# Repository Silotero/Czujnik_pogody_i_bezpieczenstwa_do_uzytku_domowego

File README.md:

# Czujnik_pogody_i_bezpieczenstwa_do_uzytku_domowego
This is a device packed with MQ-7 (CO gas sensor), MQ-2 (smoke sensor), IR fire detector, as well as AHT20 (temperature and humidity sensor), along with the BMP280 (pressure sensor).

It is battery powered with USB-C non PD charging, usiong the MCP73831 battery charge IC, capable of charging the battery with 500 mA, with an AP9101 battery protection IC. The microcontroller used in this project is a barebone ESP32-C3, with external 4 MB of FLASH memory, using QSPI. The power coming from the battery gets passed to the PAM2423 boost converter circuit that boosts the battery voltage up to 5V. The 2 devices that use 5V (MQ-7 and MQ-2) are powered directly out of that output, while the rest such as the ESP32-C3, its FLASH memory, along with the AHT20 and BMP280 gets their 3.3V voltage out of a AP2114HA LDO

The ESP32-C3 RF pin is connected to an external antenna connector (IPEX4), used for transmitting data wirelessly.

The project is meant for use with a MQTT setup for data collection on a server type device.

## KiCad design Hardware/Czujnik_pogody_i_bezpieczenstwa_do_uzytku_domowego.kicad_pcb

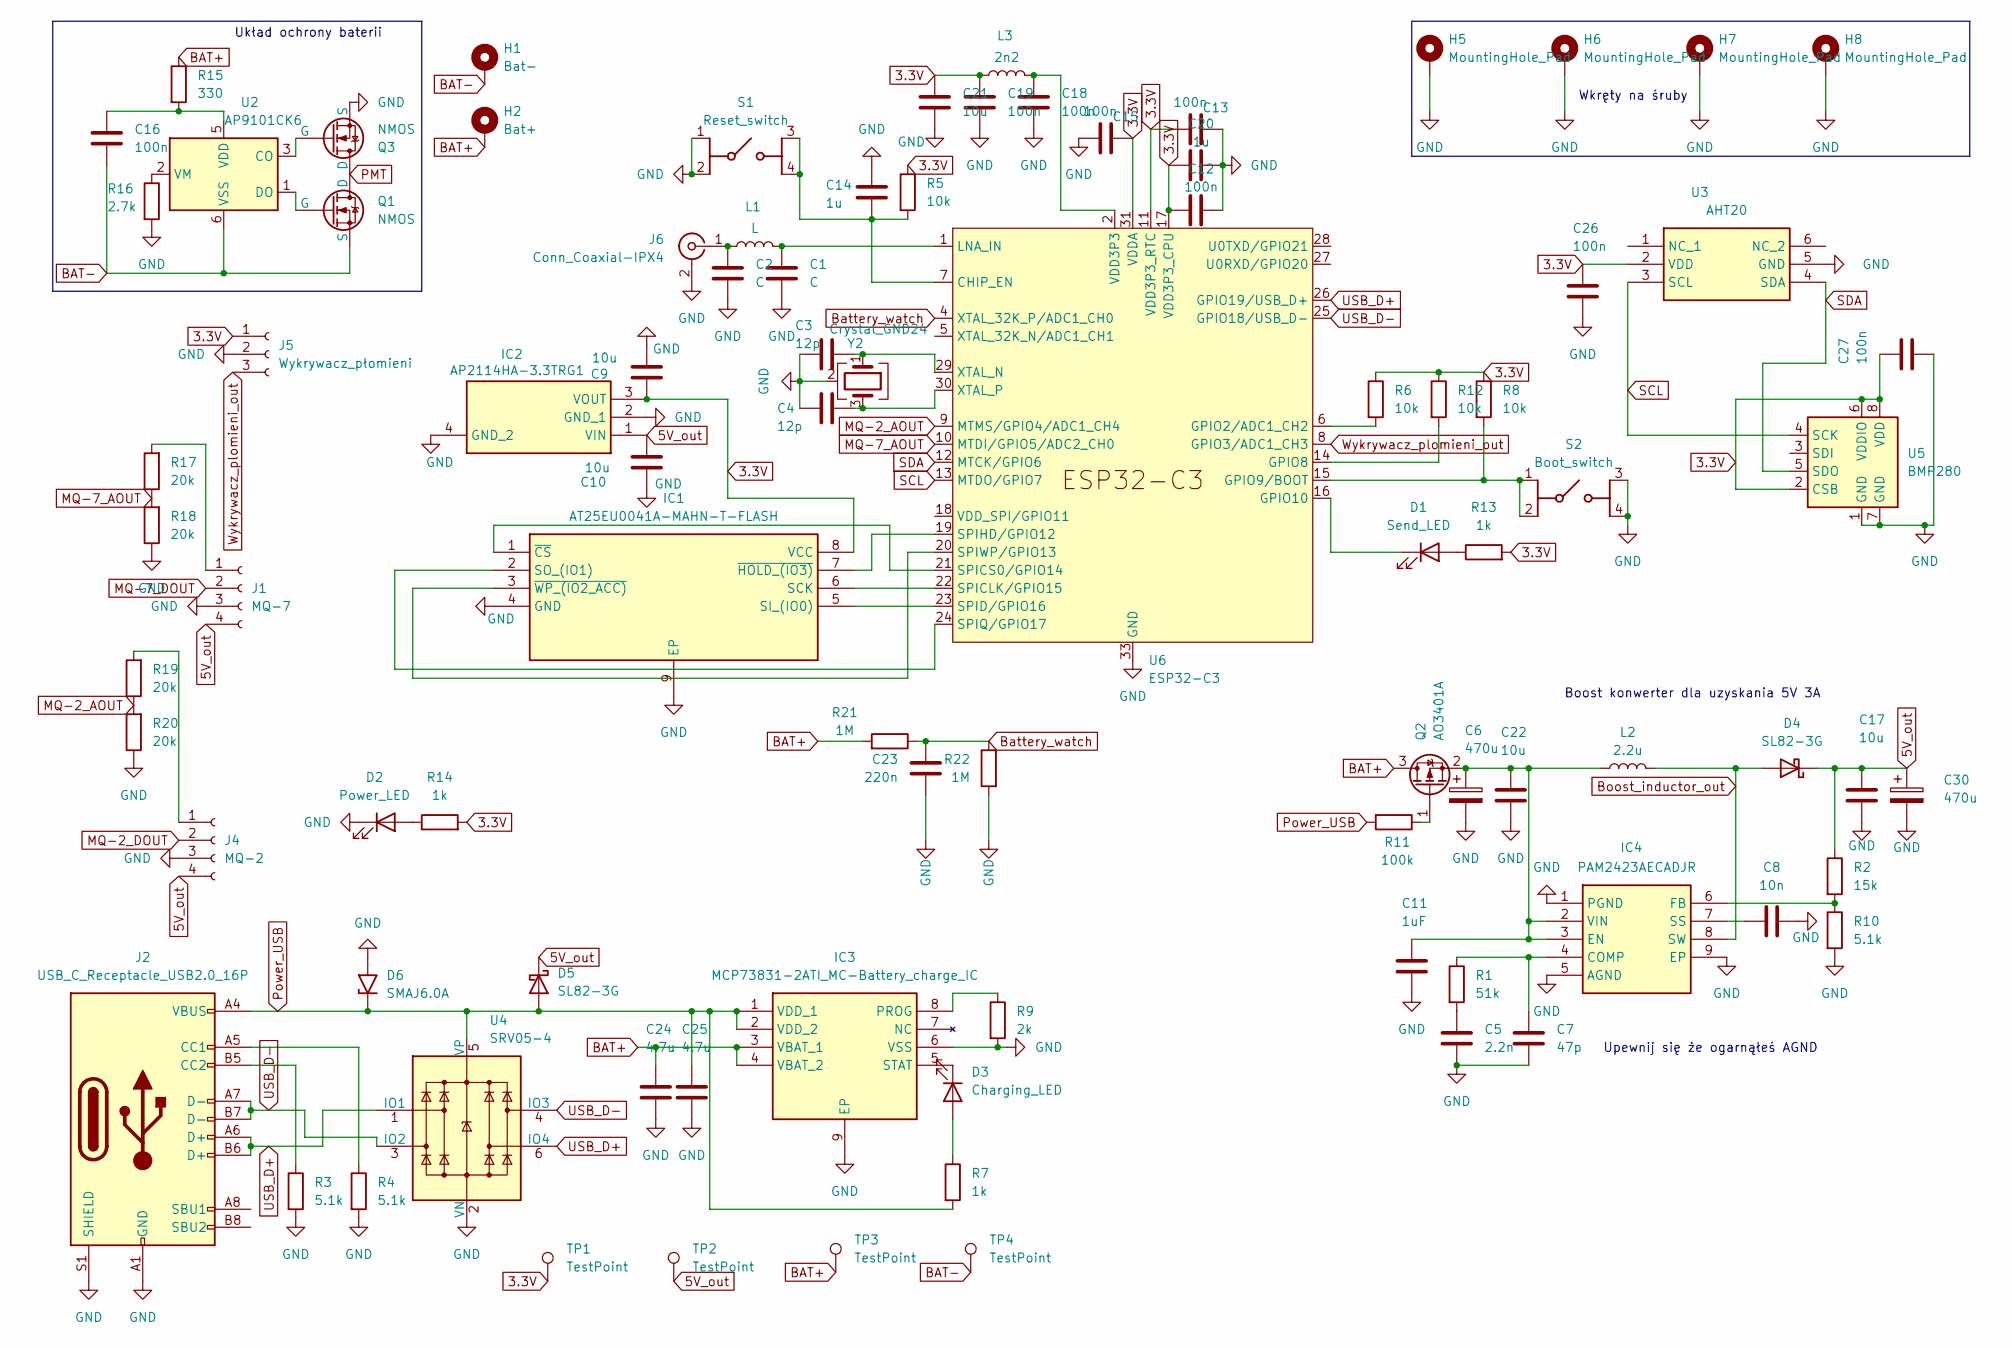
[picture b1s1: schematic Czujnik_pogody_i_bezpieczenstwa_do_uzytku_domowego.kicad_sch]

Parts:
C1, C2: C; C_0603_1608Metric
C3, C4: 12p; C_0603_1608Metric
C5: 2.2n; C_0603_1608Metric
C6, C30: 470u; CP_Radial_D10.0mm_P5.00mm
C7: 47p; C_0603_1608Metric
C8: 10n; C_0603_1608Metric
C9, C10, C17, C21, C22: 10u; C_0603_1608Metric
C11: 1uF; C_0603_1608Metric
C12, C13, C15, C16, C18, C19, C26, C27: 100n; C_0603_1608Metric
C14, C20: 1u; C_0603_1608Metric
C23: 220n; C_0603_1608Metric
C24, C25: 4.7u; C_0603_1608Metric
D1: Send_LED; LED_0603_1608Metric
D2: Power_LED; LED_0603_1608Metric
D3: Charging_LED; LED_0603_1608Metric
D4, D5: SL82-3G; D_SMC
D6: SMAJ6.0A; D_SMA
H1: Bat-; MountingHole_2.2mm_M2_DIN965_Pad_TopBottom
H2: Bat+; MountingHole_2.2mm_M2_DIN965_Pad_TopBottom
H5, H6, H7, H8: MountingHole_Pad; MountingHole_2.2mm_M2_DIN965_Pad
IC1: AT25EU0041A-MAHN-T-FLASH; SON50P300X200X60-9N-D; Manufacturer_Part_Number AT25EU0041A-MAHN-T; Mouser Part Number 968-AT25EU0041AMAHNT
IC2: AP2114HA-3.3TRG1; SOT230P700X180-4N; Manufacturer_Part_Number AP2114HA-3.3TRG1; Mouser Part Number 621-AP2114HA-3.3TRG1
IC3: MCP73831-2ATI_MC-Battery_charge_IC; SON50P300X200X100-9N-D; Manufacturer_Part_Number MCP73831-2ATI/MC; Mouser Part Number 579-MCP73831-2ATI/MC
IC4: PAM2423AECADJR; PAM2421AECADJR; Manufacturer_Part_Number PAM2421AECADJR; Mouser Part Number 621-PAM2421AECADJR
J1: MQ-7; PinSocket_1x04_P2.54mm_Vertical
J2: USB_C_Receptacle_USB2.0_16P; USB_C_Receptacle_GCT_USB4105-xx-A_16P_TopMnt_Horizontal
J4: MQ-2; PinSocket_1x04_P2.54mm_Vertical
J5: Wykrywacz_płomieni; PinSocket_1x03_P2.54mm_Vertical
J6: Conn_Coaxial-IPX4; IPX4
L1: L; L_0603_1608Metric
L2: 2.2u; DR127
L3: 2n2; L_0603_1608Metric
Q1, Q3: NMOS; SOP-8_3.76x4.96mm_P1.27mm
Q2: AO3401A; SOT-23
R1: 51k; R_0805_2012Metric
R2: 15k; R_0805_2012Metric
R3, R4, R10: 5.1k; R_0805_2012Metric
R5, R6, R8, R12: 10k; R_0805_2012Metric
R7, R13, R14: 1k; R_0805_2012Metric
R9: 2k; R_0805_2012Metric
R11: 100k; R_0805_2012Metric
R15: 330; R_0805_2012Metric
R16: 2.7k; R_0805_2012Metric
R17, R18, R19, R20: 20k; R_0805_2012Metric
R21, R22: 1M; R_0805_2012Metric
S1: Reset_switch; RKC2SJM170SMTRLFS; Manufacturer_Part_Number RKC2SJM170SMTRLFS; Mouser Part Number 611-KC2SJM170SMTRLFS
S2: Boot_switch; RKC2SJM170SMTRLFS; Manufacturer_Part_Number RKC2SJM170SMTRLFS; Mouser Part Number 611-KC2SJM170SMTRLFS
TP1, TP2, TP3, TP4: TestPoint; TestPoint_THTPad_D1.0mm_Drill0.5mm
U2: AP9101CK6; SOT-23-6
U3: AHT20; Manufacturer_Part_Number AHT20
U4: SRV05-4; SOT-23-6
U5: BMP280; Bosch_LGA-8_2x2.5mm_P0.65mm_ClockwisePinNumbering
U6: ESP32-C3; QFN-32-1EP_5x5mm_P0.5mm_EP3.45x3.45mm
Y2: Crystal_GND24; Crystal_SMD_3225-4Pin_3.2x2.5mm

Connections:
3.3V: C9.1, C12.1, C13.1, C15.2, C19.1, C20.1, C21.1, C26.1, C27.1, IC1.8 (VCC), IC2.3 (VOUT), J5.1, L3.1, R5.1, R6.1, R8.1, R12.1, R13.2, R14.2, TP1.1, U3.2 (VDD), U5.2 (CSB), U5.6 (VDDIO), U5.8 (VDD), U6.11 (VDD3P3_RTC), U6.17 (VDD3P3_CPU), U6.31 (VDDA), U6.32 (VDDA); also elsewhere on the board
5V_out: C10.2, C17.1, C30.1, D4.1 (K), D5.1 (K), IC2.1 (VIN), J1.4, J4.4, R2.1, TP2.1; also elsewhere on the board
BAT+: C24.1, H2.1, IC3.3 (VBAT_1), IC3.4 (VBAT_2), Q2.3 (D), R15.1, R21.2, TP3.1; also elsewhere on the board
BAT-: C16.2, H1.1, Q1.3 (S), TP4.1, U2.6 (VSS); also elsewhere on the board
Battery_watch: C23.1, R21.1, R22.1, U6.4 (XTAL_32K_P/ADC1_CH0)
Boost_inductor_out: D4.2 (A), IC4.8 (SW), L2.2
GND: C1.2, C2.1, C3.2, C4.2, C5.2, C6.2, C7.2, C8.2, C9.2, C10.1, C11.2, C12.2, C13.2, C14.2, C15.1, C17.2, C18.2, C19.2, C20.2, C21.2, C22.2, C23.2, C24.2, C25.2, C26.2, C27.2, C30.2, D2.1 (K), D6.2 (A2), H5.1, H6.1, H7.1, H8.1, IC1.4 (GND), IC1.9 (EP), IC2.2 (GND_1), IC2.4 (GND_2), IC3.6 (VSS), IC3.9 (EP), IC4.1 (PGND), IC4.5 (AGND), IC4.9 (EP), J1.3, J2.A1 (GND), J2.A12 (GND), J2.B1 (GND), J2.B12 (GND), J2.S1 (SHIELD), J4.3, J5.2, J6.2 (Ext), Q3.3 (S), R3.2, R4.2, R9.2, R10.2, R16.2, R18.1, R20.1, R22.2, S1.1 (COM_1), S1.2 (COM_2), S2.3 (NO_1), S2.4 (NO_2), U3.5 (GND), U4.2 (VN), U5.1 (GND), U5.7 (GND), U6.33 (GND), Y2.2 (G), Y2.4 (G)
MQ-2_AOUT: R19.1, R20.2, U6.9 (MTMS/GPIO4/ADC1_CH4)
MQ-2_DOUT: J4.2
MQ-7_AOUT: R17.1, R18.2, U6.10 (MTDI/GPIO5/ADC2_CH0)
MQ-7_DOUT: J1.2
unnamed: C5.1, R1.2
unnamed: C18.1, L3.2, U6.2 (VDD3P3), U6.3 (VDD3P3)
unnamed: D1.2 (A), R13.1
unnamed: D1.1 (K), U6.16 (GPIO10)
unnamed: D2.2 (A), R14.1
unnamed: D3.2 (A), R7.1
unnamed: D3.1 (K), IC3.5 (STAT)
unnamed: IC1.6 (SCK), U6.22 (SPICLK/GPIO15)
unnamed: IC1.5 (SI_(IO0)), U6.23 (SPID/GPIO16)
unnamed: IC1.2 (SO_(IO1)), U6.24 (SPIQ/GPIO17)
unnamed: IC1.1 (~CS), U6.21 (SPICS0/GPIO14)
unnamed: IC1.7 (~HOLD_(IO3)), U6.19 (SPIHD/GPIO12)
unnamed: IC1.3 (~WP_(IO2_ACC)), U6.20 (SPIWP/GPIO13)
unnamed: IC3.8 (PROG), R9.1
unnamed: C7.1, IC4.4 (COMP), R1.1
unnamed: C6.1, C11.1, C22.1, IC4.2 (VIN), IC4.3 (EN), L2.1, Q2.2 (S)
unnamed: IC4.6 (FB), R2.2, R10.1
unnamed: C8.1, IC4.7 (SS)
unnamed: J1.1, R17.2
unnamed: J2.A5 (CC1), R4.1
unnamed: J2.B5 (CC2), R3.1
unnamed: J4.1, R19.2
unnamed: C2.2, J6.1 (In), L1.1
unnamed: Q1.2 (G), U2.1 (DO)
unnamed: Q2.1 (G), R11.1
unnamed: Q3.2 (G), U2.3 (CO)
unnamed: C14.1, R5.2, S1.3 (NO_1), S1.4 (NO_2), U6.7 (CHIP_EN)
unnamed: R8.2, S2.1 (COM_1), S2.2 (COM_2), U6.15 (GPIO9/BOOT)
unnamed: C16.1, R15.2, U2.5 (VDD)
unnamed: R16.1, U2.2 (VM)
unnamed: R6.2, U6.6 (GPIO2/ADC1_CH2)
unnamed: R12.2, U6.14 (GPIO8)
unnamed: C1.1, L1.2, U6.1 (LNA_IN)
unnamed: C3.1, U6.29 (XTAL_N), Y2.1
unnamed: C4.1, U6.30 (XTAL_P), Y2.3
PMT: Q1.1 (D), Q3.1 (D)
Power_USB: C25.1, D5.2 (A), D6.1 (A1), IC3.1 (VDD_1), IC3.2 (VDD_2), J2.A4 (VBUS), J2.A9 (VBUS), J2.B4 (VBUS), J2.B9 (VBUS), R7.2, R11.2, U4.5 (VP)
SCL: U3.3 (SCL), U5.4 (SCK), U6.13 (MTDO/GPIO7)
SDA: U3.4 (SDA), U5.5 (SDO), U6.12 (MTCK/GPIO6)
USB_D+: J2.A6 (D+), J2.B6 (D+), U4.1 (IO1), U4.6 (IO4), U6.26 (GPIO19/USB_D+)
USB_D-: J2.A7 (D-), J2.B7 (D-), U4.3 (IO2), U4.4 (IO3), U6.25 (GPIO18/USB_D-)
Wykrywacz_plomieni_out: J5.3, U6.8 (GPIO3/ADC1_CH3)

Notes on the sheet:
Układ ochrony baterii
Wkręty na śruby
Boost konwerter dla uzyskania 5V 3A
Upewnij się że ogarnąłeś AGND

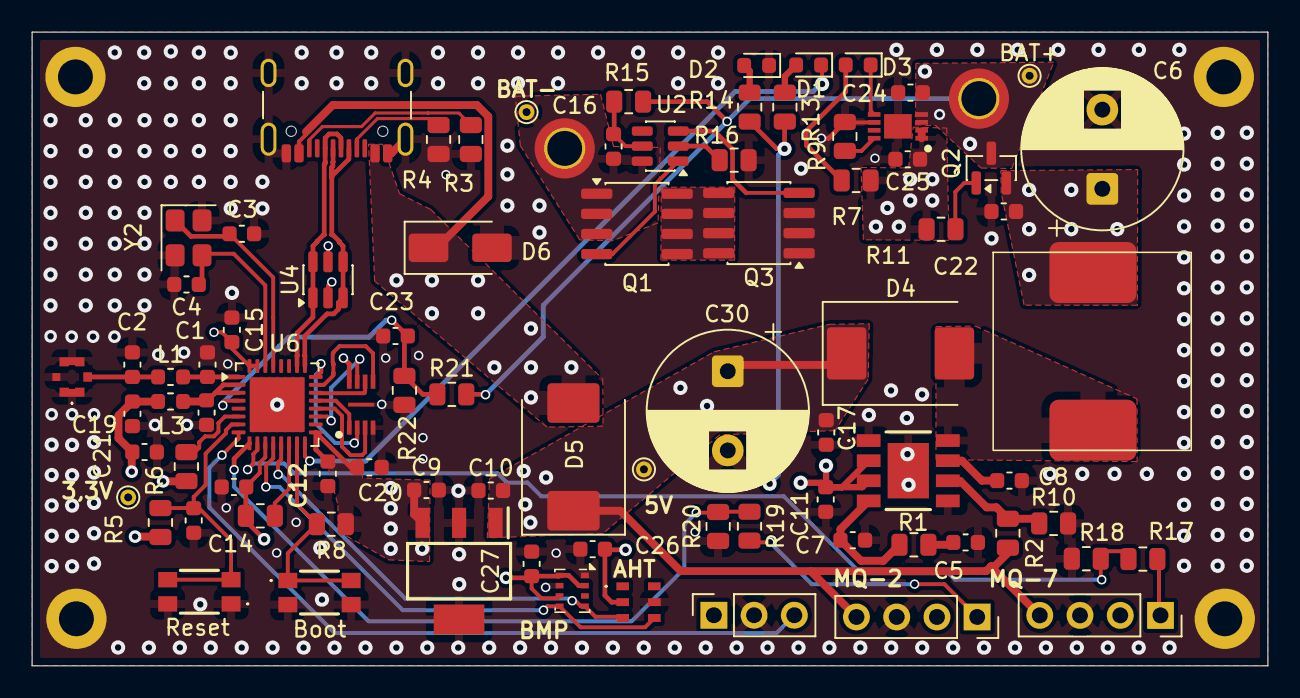
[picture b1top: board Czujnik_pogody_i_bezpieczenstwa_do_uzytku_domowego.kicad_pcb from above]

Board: 4 copper layers, 78.0 x 40.0 mm, 89 parts (0 on the bottom side), 51 nets.

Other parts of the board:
3,3V, 5V: TestPoint; TestPoint_THTPad_D1.0mm_Drill0.5mm
BAT+: TestPoint; TestPoint_THTPad_D1.0mm_Drill0.5mm
BAT-: TestPoint; TestPoint_THTPad_D1.0mm_Drill0.5mm

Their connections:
3.3V: 3,3V.1; also elsewhere on the board
5V_out: 5V.1; also elsewhere on the board
BAT+: BAT+.1; also elsewhere on the board
BAT-: BAT-.1; also elsewhere on the board

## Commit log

2026-05-22 Added git ignore, created kicad start files
2026-05-25 Update po dużej ilości pracy
    Schemat raczej już skończony.
2026-05-27 Projekt ukończony
2026-05-27 Dodano zdjęcia z obliczeń pod usb i antene
